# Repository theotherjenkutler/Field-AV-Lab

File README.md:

<h2>Field AV Lab</h2>

Field AV Lab is an electronics prototyping system geared towards circuit education and 
rapid prototyping for AV performance circuits. It has two 3.5mm IO, a dedicated headphone 
amplifier/audio output and VGA input/output for CHA/V style VGA video hacking. There are 
on board potentiometers, a light sensitive resistor and two LEDS for visualizing LFOs and 
general sanity checks. It is meant to pick up where the now discontinued Om Synth left off.

This design is a collaboration between Wavefield (wavefield.media) and Jen Kutler (jenkutler.com)
based on the Om Synth by Peter Edwards of Casper Electronics (casperelectronics.com) combined with
the CHA/V by Jonas Bers (jonasbers.com) PCB Artwork by Paloma Kop (palomakop.tv).

Instructional videos for the Om Synth and 'recipes' translate to this board e.g.
<br>https://www.youtube.com/watch?v=FaoJaLmZaL4
<br>https://www.youtube.com/watch?v=t7JYOIYqMEY
<br>https://www.youtube.com/watch?v=ECSYLTB_sbw

It also offers a lower cost point of entry than the LABOR but can be used practically in the
same way for instructional videos like these:
<br>https://www.youtube.com/watch?v=Xbl1xwFR3eg

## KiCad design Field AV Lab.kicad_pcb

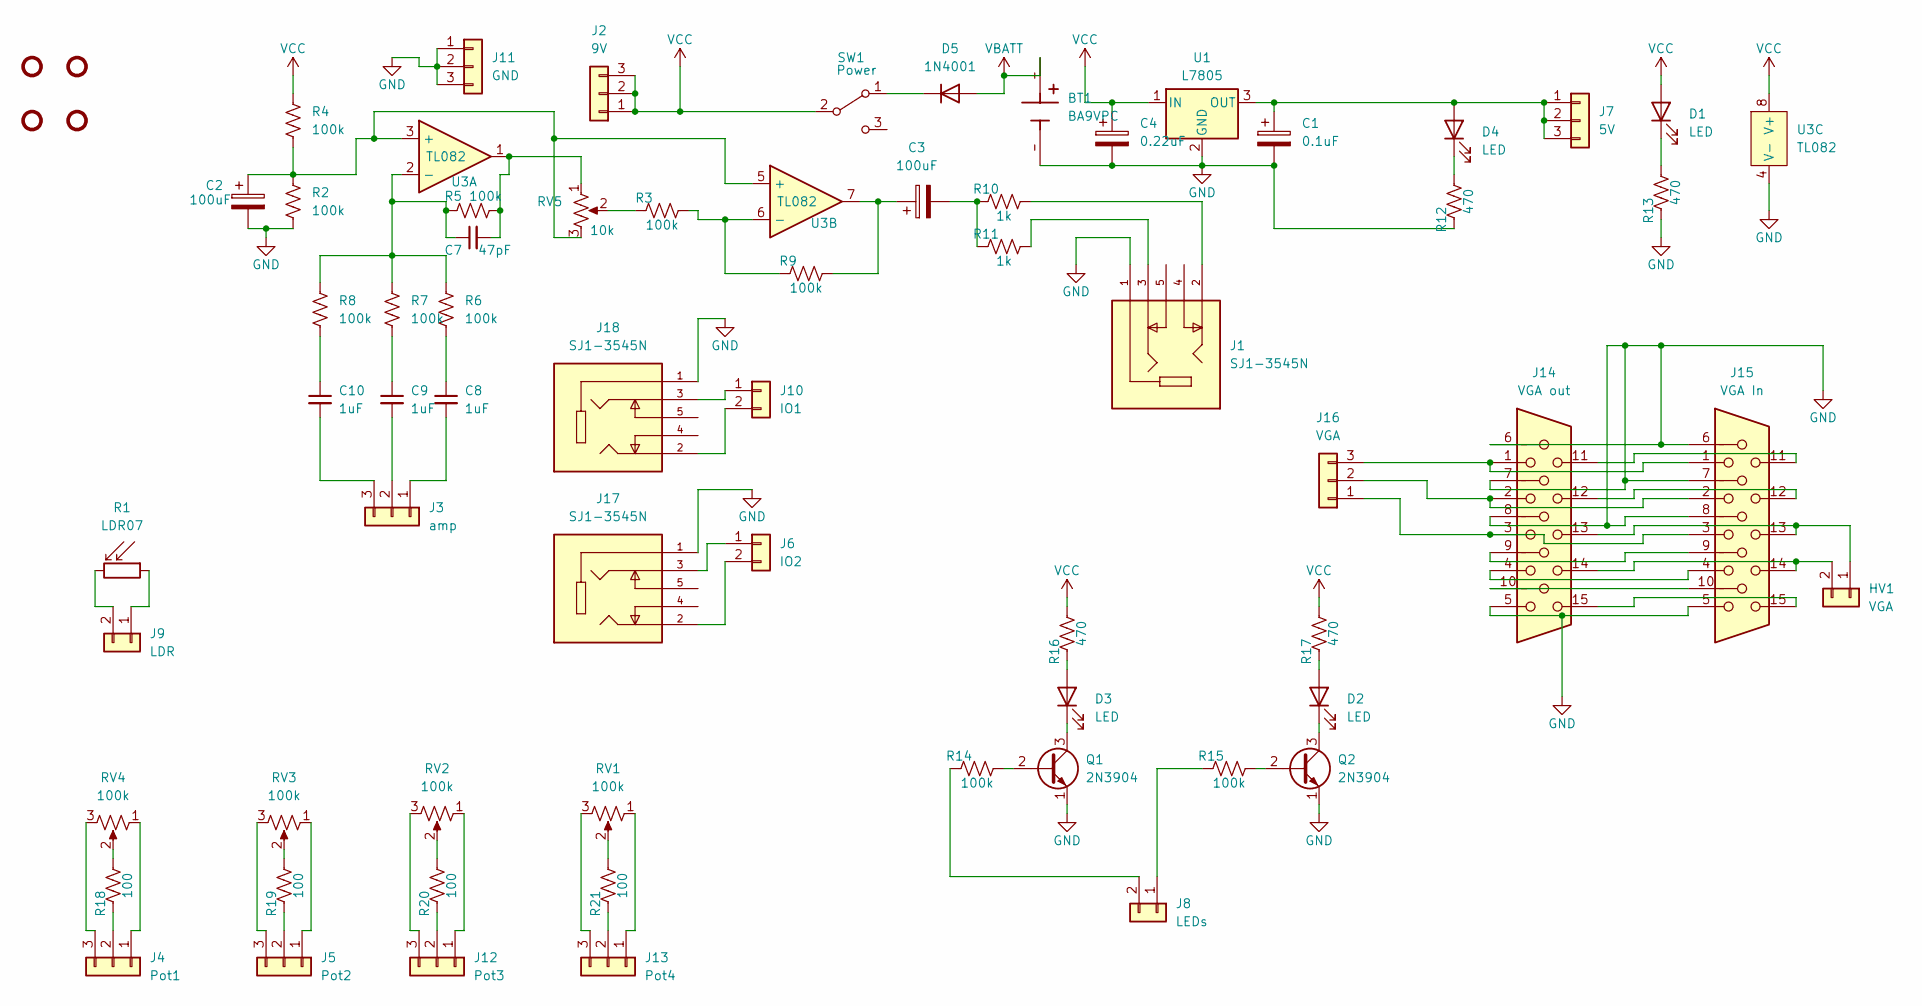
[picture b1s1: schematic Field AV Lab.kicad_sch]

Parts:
BT1: BA9VPC; BAT_BA9VPC; PARTREV E
C1: 0.1uF; CP_Radial_D5.0mm_P2.50mm
C2, C3: 100uF; CP_Radial_D5.0mm_P2.50mm
C4: 0.22uF; CP_Radial_D5.0mm_P2.50mm
C7: 47pF; C_Disc_D5.0mm_W2.5mm_P2.50mm
C8, C9, C10: 1uF; C_Disc_D5.0mm_W2.5mm_P2.50mm
D1, D2, D3, D4: LED; LED_D3.0mm
D5: 1N4001; D_DO-41_SOD81_P10.16mm_Horizontal
HV1: VGA; PinHeader_1x02_P2.54mm_Vertical; Part Number 1-0201FBV0T
J1, J17, J18: SJ1-3545N; CUI_SJ1-3545N; PARTREV 1.03
J2: 9V; PinHeader_1x03_P2.54mm_Vertical; Part Number 1-0301FBV0T
J3: amp; PinHeader_1x03_P2.54mm_Vertical; Part Number 1-0301FBV0T
J4: Pot1; PinHeader_1x03_P2.54mm_Vertical; Part Number 1-0301FBV0T
J5: Pot2; PinHeader_1x03_P2.54mm_Vertical; Part Number 1-0301FBV0T
J6: IO2; PinHeader_1x02_P2.54mm_Vertical; Part Number 1-0201FBV0T
J7: 5V; PinHeader_1x03_P2.54mm_Vertical; Part Number 1-0301FBV0T
J8: LEDs; PinHeader_1x02_P2.54mm_Vertical; Part Number 1-0201FBV0T
J9: LDR; PinHeader_1x02_P2.54mm_Vertical; Part Number 1-0201FBV0T
J10: IO1; PinHeader_1x02_P2.54mm_Vertical; Part Number 1-0201FBV0T
J11: GND; PinHeader_1x03_P2.54mm_Vertical; Part Number 1-0301FBV0T
J12: Pot3; PinHeader_1x03_P2.54mm_Vertical; Part Number 1-0301FBV0T
J13: Pot4; PinHeader_1x03_P2.54mm_Vertical; Part Number 1-0301FBV0T
J14: VGA out; DSUB-15_Socket_Vertical_P2.77x2.84mm
J15: VGA In; DSUB-15_Socket_Vertical_P2.77x2.84mm
J16: VGA; PinHeader_1x03_P2.54mm_Vertical; Part Number 1-0301FBV0T
Q1, Q2: 2N3904; TO-92_Inline
R1: LDR07; R_LDR_5.1x4.3mm_P3.4mm_Vertical
R2, R3, R4, R5, R6, R7, R8, R9, R14, R15: 100k; R_Axial_DIN0204_L3.6mm_D1.6mm_P5.08mm_Horizontal
R10, R11: 1k; R_Axial_DIN0204_L3.6mm_D1.6mm_P5.08mm_Horizontal
R12, R13, R16, R17: 470; R_Axial_DIN0204_L3.6mm_D1.6mm_P5.08mm_Horizontal
R18, R19, R20, R21: 100; R_Axial_DIN0204_L3.6mm_D1.6mm_P5.08mm_Horizontal
RV1, RV2, RV3, RV4: 100k; Potentiometer_TT_P0915N
RV5: 10k; Potentiometer_TT_P0915N
ST1, ST2, ST3, ST4: Standoff
SW1: Power; Slide_SPDT_PTH_11.6x4.0mm
U1: L7805; TO-220-3
U3: TL082; DIP-8_W7.62mm; Part Number TL082CPT; JLCPCB ID C2652280

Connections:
GND: BT1.-, C1.2, C2.2, C4.2, J1.1, J11.1, J11.2, J11.3, J14.5, J14.6, J14.7, J14.8, J15.5, J15.6, J15.7, J15.8, J17.1, J18.1, Q1.1 (E), Q2.1 (E), R2.2, R12.1, R13.1, U1.2 (GND), U3.4 (V-)
unnamed: C3.1, R9.2, U3.7
unnamed: C3.2, R10.1, R11.1
unnamed: C7.2, R5.1, RV5.1, U3.1
unnamed: C8.1, R6.2
unnamed: C9.1, R7.2
unnamed: C10.1, R8.2
unnamed: D1.1 (K), R13.2
unnamed: D2.2 (A), R17.1
unnamed: D2.1 (K), Q2.3 (C)
unnamed: D3.2 (A), R16.1
unnamed: D3.1 (K), Q1.3 (C)
unnamed: C1.1, D4.2 (A), J7.1, J7.2, J7.3, U1.3 (OUT)
unnamed: D4.1 (K), R12.2
unnamed: D5.1 (K), SW1.1 (A)
unnamed 15: HV1.1, J14.13, J15.13; also elsewhere on the board
unnamed 16: HV1.2, J14.14, J15.14; also elsewhere on the board
unnamed: J1.2, R10.2
unnamed: J1.3, R11.2
unnamed: C8.2, J3.1
unnamed: C9.2, J3.2
unnamed: C10.2, J3.3
unnamed: J4.1, RV4.1
unnamed: J4.2, R18.1
unnamed: J4.3, RV4.3
unnamed: J5.1, RV3.1
unnamed: J5.2, R19.1
unnamed: J5.3, RV3.3
unnamed: J6.1, J17.3
unnamed: J6.2, J17.2
unnamed: J8.1, R15.1
unnamed: J8.2, R14.1
unnamed: J9.1, R1.1
unnamed: J9.2, R1.2
unnamed: J10.1, J18.3
unnamed: J10.2, J18.2
unnamed: J12.1, RV2.1
unnamed: J12.2, R20.1
unnamed: J12.3, RV2.3
unnamed: J13.1, RV1.1
unnamed: J13.2, R21.1
unnamed: J13.3, RV1.3
unnamed: J14.4, J15.4
unnamed: J14.9, J15.9
unnamed: J14.10, J15.10
unnamed: J14.11, J15.11
unnamed: J14.12, J15.12
unnamed: J14.15, J15.15
unnamed 48: J14.3, J15.3, J16.1; also elsewhere on the board
unnamed 49: J14.2, J15.2, J16.2; also elsewhere on the board
unnamed 50: J14.1, J15.1, J16.3; also elsewhere on the board
unnamed: Q1.2 (B), R14.2
unnamed: Q2.2 (B), R15.2
unnamed: R3.1, RV5.2
unnamed: R18.2, RV4.2
unnamed: R19.2, RV3.2
unnamed: R20.2, RV2.2
unnamed: R21.2, RV1.2
unnamed: C2.1, R2.1, R4.2, RV5.3, U3.3 (+), U3.5 (+)
unnamed: C7.1, R5.2, R6.1, R7.1, R8.1, U3.2 (-)
unnamed: R3.2, R9.1, U3.6 (-)
VBATT: BT1.+, D5.2 (A)
VCC: C4.1, D1.2 (A), J2.1, J2.2, J2.3, R4.1, R16.2, R17.2, SW1.2 (B), U1.1 (IN), U3.8 (V+)

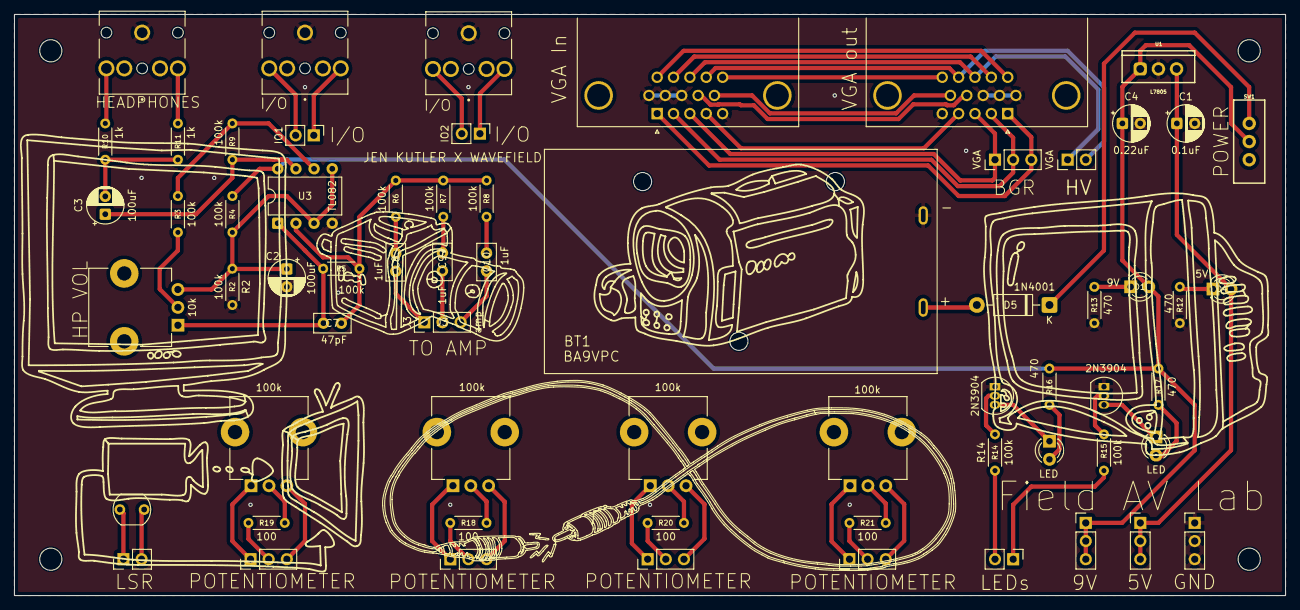
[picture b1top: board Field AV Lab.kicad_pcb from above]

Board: 2 copper layers, 177.8 x 81.3 mm, 68 parts (0 on the bottom side), 63 nets.

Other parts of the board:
HV: VGA; PinHeader_1x02_P2.54mm_Vertical
RGB: VGA; PinHeader_1x03_P2.54mm_Vertical

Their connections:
unnamed 15: HV.1; also elsewhere on the board
unnamed 16: HV.2; also elsewhere on the board
unnamed 48: RGB.1; also elsewhere on the board
unnamed 49: RGB.2; also elsewhere on the board
unnamed 50: RGB.3; also elsewhere on the board

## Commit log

2026-04-28 Create README with title and placeholder description
    Add initial content to README with title and image.
2026-04-28 Fix HTML tag in README header
2026-04-28 Enhance README with Field AV Lab description
    Added detailed description of the Field AV Lab, including its features, collaboration credits, and instructional video links.
2026-04-28 Improve formatting of instructional video links
    Updated video links with line breaks for better formatting.
